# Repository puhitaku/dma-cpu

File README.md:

# dma-cpu

CPU made of DMA on Raspberry Pi Pico.

The DMA controller in the RP2 microcontroller family (RP2040, RP2350, and
compatible chips) is Turing-complete. This project builds a full toolchain
for it: an emulator, an assembler/linker, a program loader, a C compiler
riding stock clang, and an xv6-derived kernel that runs entirely on DMA
channels. See `prompts/overview.md` for the design analysis, the phased
development plan, and references.

## Layout

The tree is split by where code runs: `host/` is the Go toolchain that runs
on your dev machine, `target/` is the C that runs on the Pico. Everything
else is docs, examples, and vendored dependencies.

### `host/` — the Go toolchain

- `host/emu/` — `dmaemu` core: a deterministic, DMA-machine-level emulator
  of the RP2 DMA subsystem (channels, triggers, chaining, DREQ credits,
  pacing timers, sniffer, atomic register aliases). Both SKUs are
  supported via `emu.Variant` (`emu.RP2040`, `emu.RP2350`) — the CTRL bit
  layout, register offsets, sizes, and DREQ numbers differ between them,
  so programs are assembled per SKU. The golden tests in
  `host/emu/machine_test.go` build the machine's ALU and control-flow
  idioms block by block, run the whole suite on both SKUs, and prove out
  the interrupt-dispatch design from `prompts/overview.md` §3.2.
- `host/dmaasm/` — the assembler: SKU-portable `.dasm` sources (labels,
  literal pools, instruction-field addressing, the ABI v0 register file
  and macro instruction set — see `references/design_docs/abi.md`) assembled into
  SKU-specific DMX executables with a symbol table. Validated on silicon:
  the HIL firmware runs assembler-produced binaries.
- `host/dmacc/` + `host/llir/` — the C toolchain: `llir` parses clang's
  LLVM IR, `dmacc` lowers it to SKU-portable `.dasm`. Differential tests
  in `host/dmacc/testdata/` pin it against host clang.
- `host/trace/` + `host/pgo/` — the measurement side: `trace` attributes
  the emulator's per-word read counts back to code (compiled function,
  block, comparison site, runtime/millicode helper) through the `.dasm`
  label stream and prints a ranked report; `pgo` holds the generated
  profile-guided settings those measurements produce (`make pgo`).
  `host/dmacc/testdata/ratchet.txt` pins the resulting sizes and cycle
  counts, and `make test` fails on any drift (`make ratchet`).
- `host/img/` — the DMX executable format (`references/design_docs/dmx.md`): builder,
  encoder/decoder, and the reference loader with Tier-2 relocation (same
  image runs at any placement). `host/fsimg/` builds xv6 filesystem images
  and the golden vfat volumes.
- `host/boards/` — deployable-target descriptors (SKU, memory partition,
  flash sections, installed apps); `host/prog/hil/` holds the HIL test
  programs as embedded `.dasm` assets.
- `host/cmd/` — the CLIs: `dmaemu` (runs a raw block image or DMX
  executable under a JSON config, reporting JSON), `dmaasm`, `dmacc`,
  `dmxgen` (builds a board's images and bakes them, with their emulator
  expectations, into the firmware header), and `sldgen` (converts images
  into slides for the viewer).

### `target/` — bare-metal C for the Pico

- `target/loader/` — the DMX loader for the RP2 side; parses DMX,
  relocates, and starts the machine. No SDK dependency; build with
  `-DDMX_TARGET_RP2350` for RP2350 (RP2040 is the default). Validated on
  both SKUs' silicon.
- `target/firmware/` — the ARM-side bootloader: it sets the clocks,
  stages the flash-resident images, loads the SRAM segments through the
  loader, starts the DMA machine and parks. Built with `HIL_DEV=1` it
  also carries the hardware-in-the-loop battery, where `dmxgen` bakes
  emulator-computed expectations into the firmware and the boot run
  reports expected-vs-observed over UART. The emulator is
  silicon-calibrated against a Pico 2; see
  `prompts/004-hw-calibration.md` for the results (all golden tests pass
  on hardware at ~10 M blocks/s).
- `target/libc/` — the DMA machine's C library: DMA-specific config and
  glue (committed) plus the vendored picolibc submodule
  (`target/libc/picolibc`) it is compiled from. `make libc` turns the
  curated picolibc sources into the IR goldens in `target/libc/ll/`,
  which `dmacc` links into programs — see `target/libc/README.md`.
  `target/game/` is the DMA-driven game console; `target/xv6/` is the
  xv6-derived kernel port (`target/xv6/PORT.md`).

### Everything else

- `docs/` — human-facing guides: how to build the firmware
  (`building-firmware.md`) and how to wire the hardware
  (`building-hardware.md`).
- `prompts/` — the phased design log: the analysis in `overview.md` and a
  per-phase results document for each step.
- `references/` — material to consult, none of it compiled here:
  `datasheets/` (the RP2040/RP2350 and peripheral datasheets),
  `design_docs/` (the project's own specs — `abi.md` and `dmx.md`), and
  source trees read rather than built — some of them the origin of a port
  that now lives under `target/`, each attributed in `LICENSE`. Contrast
  `target/libc/picolibc`, which *is* compiled and linked. The reference
  article stays untracked (see Coding rules in `prompts/overview.md`).
- `examples/` — standalone programs built through the toolchain.
- `hw/` — KiCad project with JLCPCB-ready production data.

## Build and test

```console
$ make build   # builds bin/dmaemu, bin/dmaasm, bin/dmacc
$ make test    # go vet + golden tests
```

Requires Go ≥ 1.26. No dependencies outside the standard library.

## Special Thanks

This project is heavily inspired by [the original idea](https://people.ece.cornell.edu/land/courses/ece4760/RP2040/C_SDK_DMA_machine/DMA_machine_rp2040.html)
published by the authors in Cornell University.

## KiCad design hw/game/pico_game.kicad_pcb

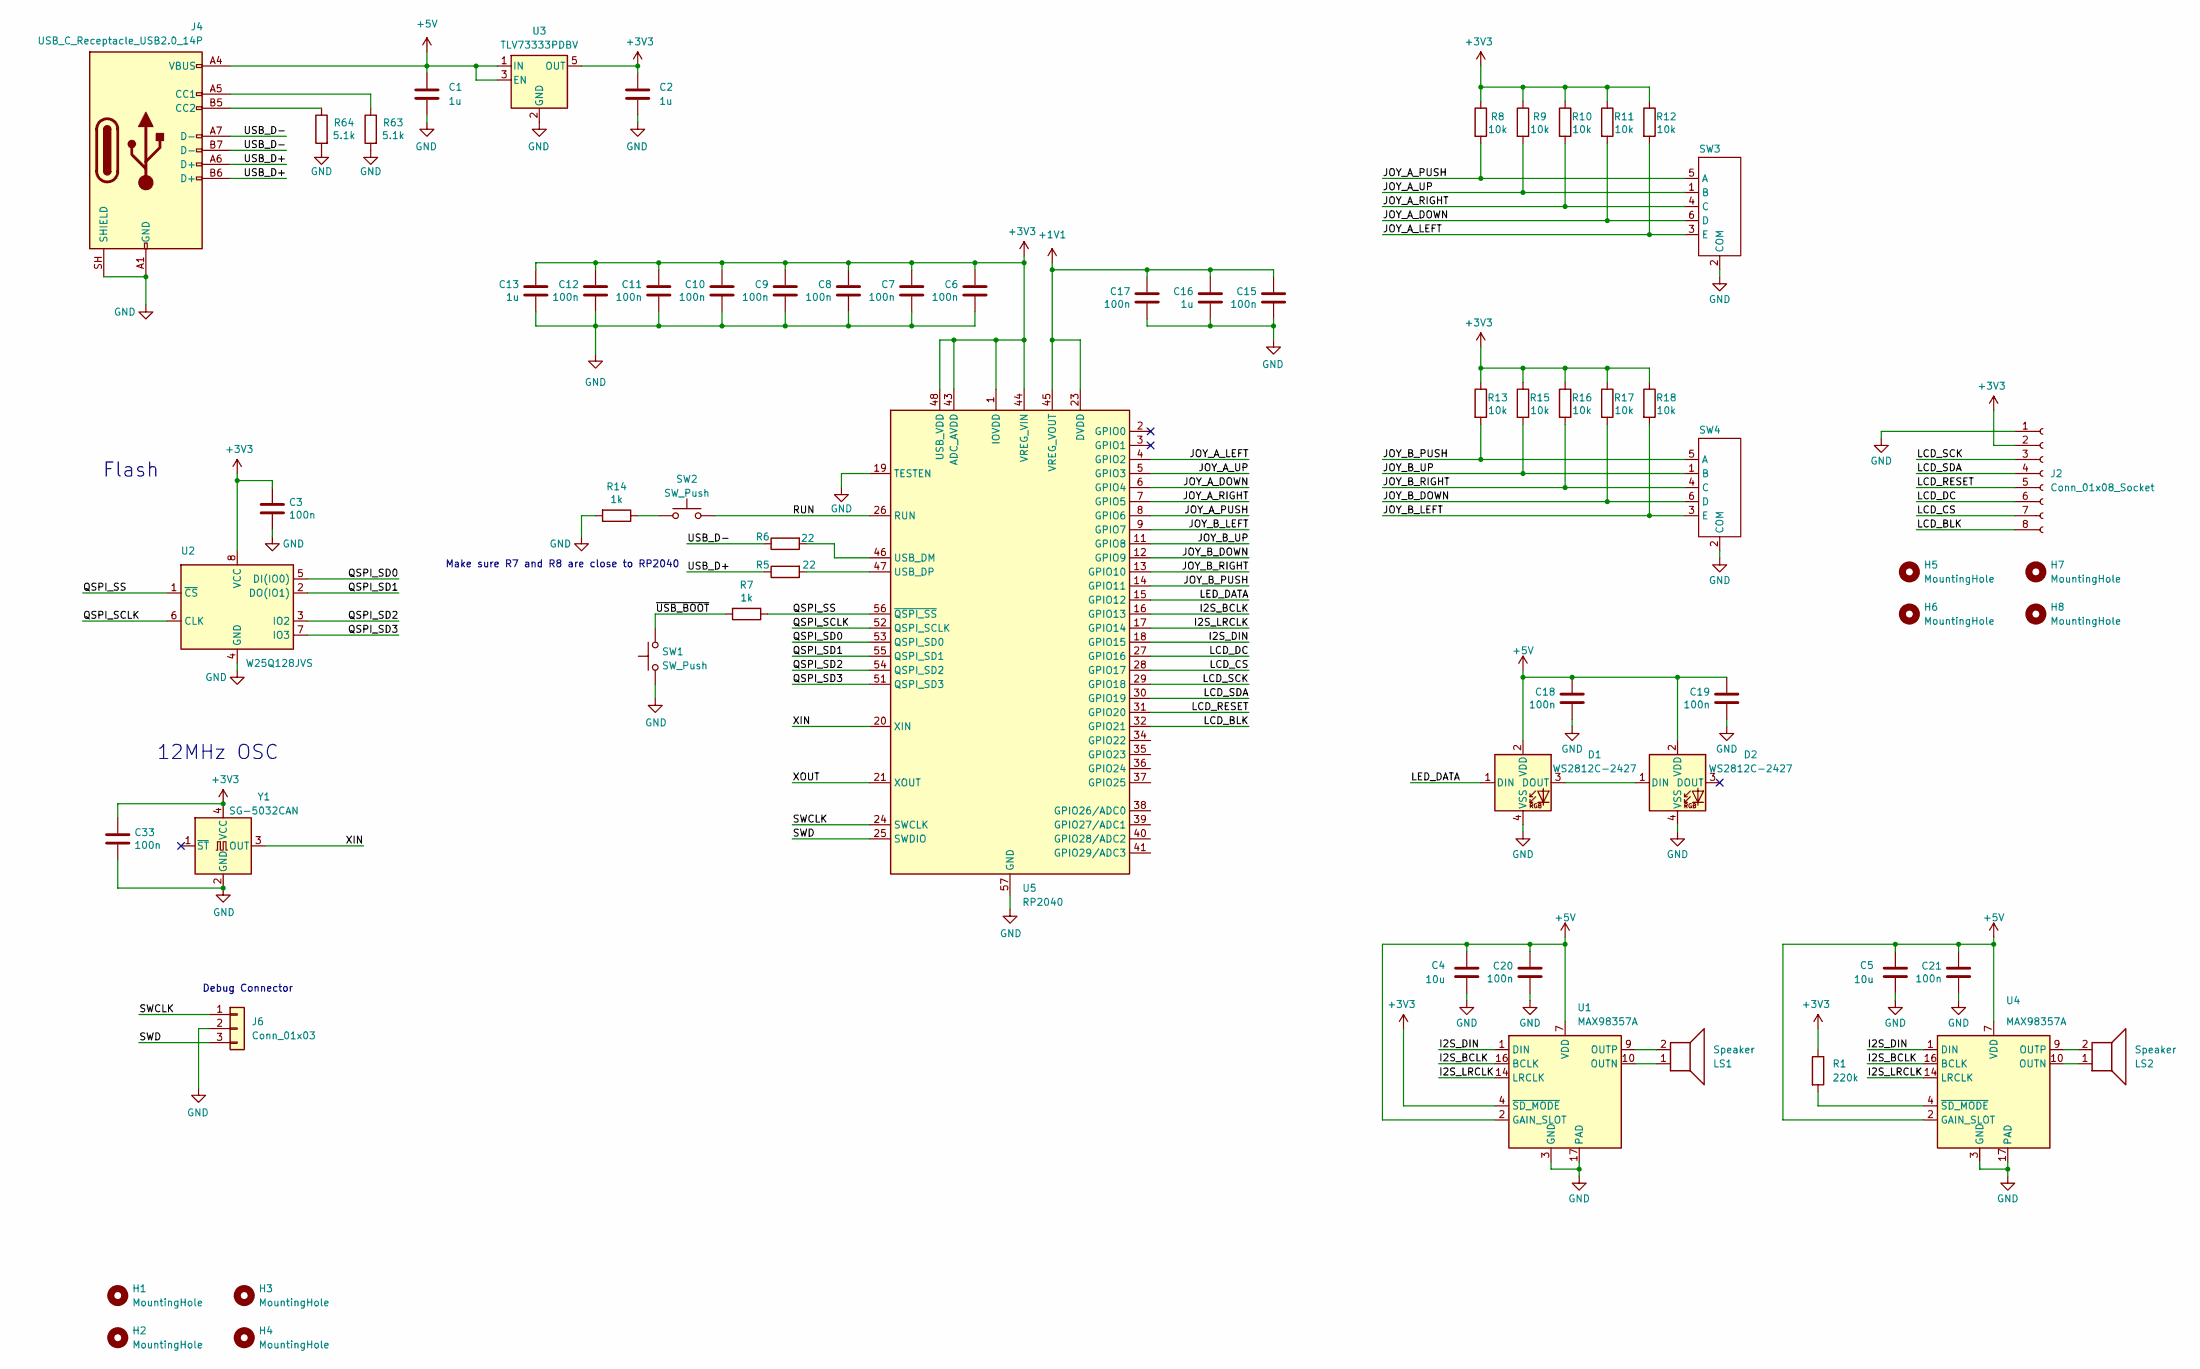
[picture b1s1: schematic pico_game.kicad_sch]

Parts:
C1, C2, C13, C16: 1u; C_0402_1005Metric; LCSC Part # C52923
C3, C6, C7, C8, C9, C10, C11, C12, C15, C17, C18, C19, C20, C21, C33: 100n; C_0402_1005Metric; LCSC Part # C307331
C4, C5: 10u; C_0603_1608Metric; LCSC Part # C96446
D1, D2: WS2812C-2427; LED_WS2812C-2427_PLCC4_2.4x2.7mm
H1, H2, H3, H4: MountingHole; MountingHole_3.2mm_M3
H5, H6, H7, H8: MountingHole; MountingHole_2.2mm_M2
J2: Conn_01x08_Socket; PinHeader_1x08_P2.54mm_Vertical
J4: USB_C_Receptacle_USB2.0_14P; USB_C_Receptacle_G-Switch_GT-USB-7010ASV; LCSC Part # C2988369
J6: Conn_01x03; PinSocket_1x03_P2.54mm_Vertical
LS1, LS2: Speaker; KLJ-01304T-08R07W; LCSC Part # C18186315
R1: 220k; R_0603_1608Metric; LCSC Part # C22961
R5, R6: 22; R_0402_1005Metric; LCSC Part # C25092
R7, R14: 1k; R_0402_1005Metric; LCSC Part # C11702
R8, R9, R10, R11, R12, R13, R15, R16, R17, R18: 10k; R_0402_1005Metric; LCSC Part # C25744
R63, R64: 5.1k; R_0402_1005Metric; LCSC Part # C25905
SW1, SW2: SW_Push; SW_SPST_TS-1088-xR020; LCSC Part # C720477
SW3, SW4: GT-TCA06F-H050-L1; LCSC Part # C3019725
U1, U4: MAX98357A; TQFN-16-1EP_3x3mm_P0.5mm_EP1.23x1.23mm; LCSC Part # C910544
U2: W25Q128JVS; SOIC-8_5.3x5.3mm_P1.27mm; LCSC Part # C97521
U3: TLV73333PDBV; SOT-23-5; LCSC Part # C134139
U5: RP2040; QFN-56-1EP_7x7mm_P0.4mm_EP3.2x3.2mm; LCSC Part # C2040
Y1: SG-5032CAN; Oscillator_SMD_SeikoEpson_SG210-4Pin_2.5x2.0mm; LCSC Part # C255991

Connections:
+1V1: C15.1, C16.1, C17.1, U5.23 (DVDD), U5.45 (VREG_VOUT), U5.50 (DVDD)
+3V3: C2.1, C3.1, C6.1, C7.1, C8.1, C9.1, C10.1, C11.1, C12.1, C13.1, C33.1, J2.2, R1.1, R8.1, R9.1, R10.1, R11.1, R12.1, R13.1, R15.1, R16.1, R17.1, R18.1, U1.4 (~SD_MODE), U2.8 (VCC), U3.5 (OUT), U5.1 (IOVDD), U5.10 (IOVDD), U5.22 (IOVDD), U5.33 (IOVDD), U5.42 (IOVDD), U5.43 (ADC_AVDD), U5.44 (VREG_VIN), U5.48 (USB_VDD), U5.49 (IOVDD), Y1.4 (VCC)
+5V: C1.1, C4.1, C5.1, C18.1, C19.1, C20.1, C21.1, D1.2 (VDD), D2.2 (VDD), J4.A4 (VBUS), J4.A9 (VBUS), J4.B4 (VBUS), J4.B9 (VBUS), U1.2 (GAIN_SLOT), U1.7 (VDD), U1.8 (VDD), U3.1 (IN), U3.3 (EN), U4.2 (GAIN_SLOT), U4.7 (VDD), U4.8 (VDD)
/I2S_BCLK: U1.16 (BCLK), U4.16 (BCLK), U5.16 (GPIO13)
/I2S_DIN: U1.1 (DIN), U4.1 (DIN), U5.18 (GPIO15)
/I2S_LRCLK: U1.14 (LRCLK), U4.14 (LRCLK), U5.17 (GPIO14)
/JOY_A_DOWN: R11.2, SW3.6 (D), U5.6 (GPIO4)
/JOY_A_LEFT: R12.2, SW3.3 (E), U5.4 (GPIO2)
/JOY_A_PUSH: R8.2, SW3.5 (A), U5.8 (GPIO6)
/JOY_A_RIGHT: R10.2, SW3.4 (C), U5.7 (GPIO5)
/JOY_A_UP: R9.2, SW3.1 (B), U5.5 (GPIO3)
/JOY_B_DOWN: R17.2, SW4.6 (D), U5.12 (GPIO9)
/JOY_B_LEFT: R18.2, SW4.3 (E), U5.9 (GPIO7)
/JOY_B_PUSH: R13.2, SW4.5 (A), U5.14 (GPIO11)
/JOY_B_RIGHT: R16.2, SW4.4 (C), U5.13 (GPIO10)
/JOY_B_UP: R15.2, SW4.1 (B), U5.11 (GPIO8)
/LCD_BLK: J2.8, U5.32 (GPIO21)
/LCD_CS: J2.7, U5.28 (GPIO17)
/LCD_DC: J2.6, U5.27 (GPIO16)
/LCD_RESET: J2.5, U5.31 (GPIO20)
/LCD_SCK: J2.3, U5.29 (GPIO18)
/LCD_SDA: J2.4, U5.30 (GPIO19)
/LED_DATA: D1.1 (DIN), U5.15 (GPIO12)
/QSPI_SCLK: U2.6 (CLK), U5.52 (QSPI_SCLK)
/QSPI_SD0: U2.5 (DI(IO0)), U5.53 (QSPI_SD0)
/QSPI_SD1: U2.2 (DO(IO1)), U5.55 (QSPI_SD1)
/QSPI_SD2: U2.3 (IO2), U5.54 (QSPI_SD2)
/QSPI_SD3: U2.7 (IO3), U5.51 (QSPI_SD3)
/QSPI_SS: R7.1, U2.1 (~CS), U5.56 (~QSPI_SS)
/RUN: SW2.2, U5.26 (RUN)
/SWCLK: J6.1, U5.24 (SWCLK)
/SWD: J6.3, U5.25 (SWDIO)
/USB_D+: J4.A6 (D+), J4.B6 (D+), R5.1
/USB_D-: J4.A7 (D-), J4.B7 (D-), R6.1
/XIN: U5.20 (XIN), Y1.3 (OUT)
/XOUT: U5.21 (XOUT)
/~USB_BOOT: R7.2, SW1.2
GND: C1.2, C2.2, C3.2, C4.2, C5.2, C6.2, C7.2, C8.2, C9.2, C10.2, C11.2, C12.2, C13.2, C15.2, C16.2, C17.2, C18.2, C19.2, C20.2, C21.2, C33.2, D1.4 (VSS), D2.4 (VSS), J2.1, J4.A1 (GND), J4.A12 (GND), J4.B1 (GND), J4.B12 (GND), J4.SH (SHIELD), J6.2, R14.2, R63.2, R64.2, SW1.1, SW3.2 (COM), SW4.2 (COM), U1.3 (GND), U1.11 (GND), U1.15 (GND), U1.17 (PAD), U2.4 (GND), U3.2 (GND), U4.3 (GND), U4.11 (GND), U4.15 (GND), U4.17 (PAD), U5.19 (TESTEN), U5.57 (GND), Y1.2 (GND)
unnamed: D1.3 (DOUT), D2.1 (DIN)
unnamed: J4.A5 (CC1), R63.1
unnamed: J4.B5 (CC2), R64.1
unnamed: R14.1, SW2.1
unnamed: LS1.1, U1.10 (OUTN)
unnamed: LS1.2, U1.9 (OUTP)
unnamed: LS2.1, U4.10 (OUTN)
unnamed: LS2.2, U4.9 (OUTP)
unnamed: R1.2, U4.4 (~SD_MODE)
unnamed: R6.2, U5.46 (USB_DM)
unnamed: R5.2, U5.47 (USB_DP)

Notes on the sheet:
Flash
12MHz OSC
Debug Connector
Make sure R7 and R8 are close to RP2040

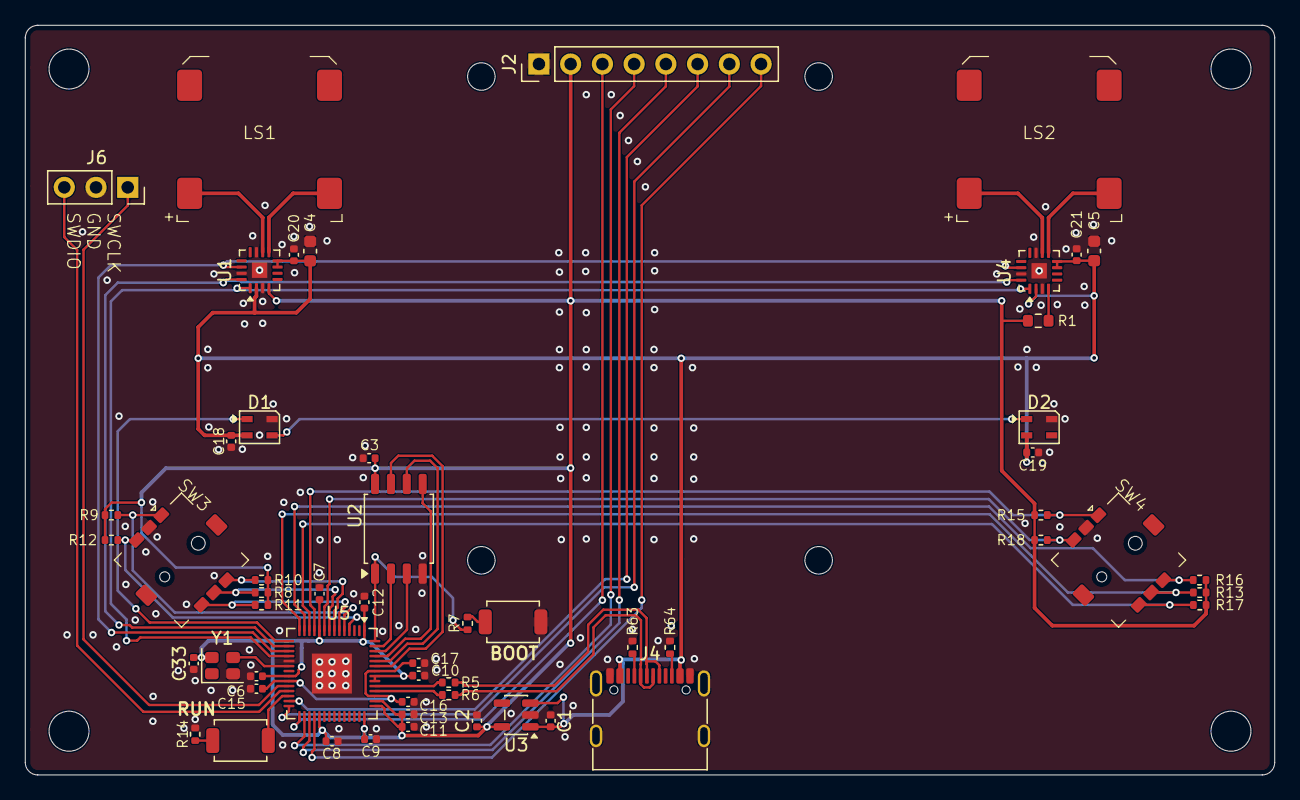
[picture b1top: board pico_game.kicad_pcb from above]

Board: 2 copper layers, 100.0 x 60.0 mm, 63 parts (0 on the bottom side), 48 nets.

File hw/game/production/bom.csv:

Designator,Footprint,Quantity,Value,LCSC Part #
"C1, C13, C16, C2",0402,4,1u,C52923
"C10, C11, C12, C15, C17, C18, C19, C20, C21, C3, C33, C6, C7, C8, C9",0402,15,100n,C307331
"C4, C5",0603,2,10u,C96446
"D1, D2",LED_WS2812C-2427_PLCC4_2.4x2.7mm,2,WS2812C-2427,
J2,PinHeader_1x08_P2.54mm_Vertical,1,Conn_01x08_Socket,
J4,USB_C_Receptacle_G-Switch_GT-USB-7010ASV,1,USB_C_Receptacle_USB2.0_14P,C2988369
J6,PinSocket_1x03_P2.54mm_Vertical,1,Conn_01x03,
"LS1, LS2",KLJ-01304T-08R07W,2,Speaker,C18186315
R1,0603,1,220k,C22961
"R10, R11, R12, R13, R15, R16, R17, R18, R8, R9",0402,10,10k,C25744
"R14, R7",0402,2,1k,C11702
"R5, R6",0402,2,22,C25092
"R63, R64",0402,2,5.1k,C25905
"SW1, SW2",SW_SPST_TS-1088-xR020,2,SW_Push,C720477
"SW3, SW4",GT-TCA06F-H050-L1,2,~,C3019725
"U1, U4",TQFN-16-1EP_3x3mm_P0.5mm_EP1.23x1.23mm,2,MAX98357A,C910544
U2,SOIC-8_5.3x5.3mm_P1.27mm,1,W25Q128JVS,C97521
U3,SOT-23-5,1,TLV73333PDBV,C134139
U5,QFN-56-1EP_7x7mm_P0.4mm_EP3.2x3.2mm,1,RP2040,C2040
Y1,Oscillator_SMD_SeikoEpson_SG210-4Pin_2.5x2.0mm,1,SG-5032CAN,C255991

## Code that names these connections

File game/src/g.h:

/* g.h: the gamepico bare-metal runtime's one header. No xv6, no libc
 * — the DMA machine drives every peripheral register itself, and the
 * ARM cores sleep. Register addresses are RP2040's (this board is
 * SKU-locked; the emulator models the same map). */
#ifndef GAME_G_H
#define GAME_G_H

typedef unsigned int uint;
typedef unsigned short ushort;
typedef unsigned char uchar;

#define W32(a) (*(volatile uint *)(a))

/* --- RP2040 fixed addresses --- */
#define IOBANK0 0x40014000u
#define PADSBANK0 0x4001C000u
#define TIMERAWL 0x40054028u /* microsecond counter, low word */
#define SPI0 0x4003C000u     /* PL022: CR0 +0, CR1 +4, DR +8, SR +C, CPSR +10 */
#define DMACH(n) (0x50000000u + (uint)(n) * 0x40u)

/* --- board wiring (see prompts/040) ---
 * Joysticks occupy GP2..GP11 but NOT in role order — the as-built
 * harness (input.c holds the tables):
 *   A: up=GP3 down=GP4 left=GP2 right=GP5 press=GP6
 *   B: up=GP8 down=GP9 left=GP7 right=GP10 press=GP11 */
#define PIN_WS 12     /* two chained WS2811 */
#define PIN_I2S_BCLK 13
#define PIN_I2S_LRCLK 14
#define PIN_I2S_DIN 15
#define PIN_LCD_DC 16
#define PIN_LCD_CS 17
#define PIN_LCD_SCK 18
#define PIN_LCD_SDA 19
#define PIN_LCD_RES 20
#define PIN_LCD_BLK 21

#define LCD_W 240
#define LCD_H 240

/* grt.c: runtime */
void uputs(const char *s);
void uputn(uint v);
void uputhex(uint v);
void numstr(char *buf, int width, uint v); /* zero-padded decimal */
void numsp(char *buf, int width, uint v);  /* space-padded decimal */
uint now_us(void);
void delay_us(uint us);
void gpio_fn(int pin, uint funcsel);
void gpio_out(int pin, int hi);
void gpio_in_init(int pin); /* enable the pull-up, once */
uint gpio_in(int pin);      /* raw masked level: nonzero = high */
void gdma_copy(uint dst, uint src, uint bytes);
void gdma_fill(uint dst, uint word, uint bytes);
void gdma_spi16(uint src, uint halfwords); /* paced pixel stream */
void gdma_rows(uint dst, uint src, uint words, int rows, uint dstride,
               uint sstride); /* 2-write row loop (AL3 trigger) */
void gdma_spi_rows(uint src, uint halfwords, int rows,
                   uint sstride); /* 1-write row loop into the SPI */

/* lcd.c */
void lcd_init(void);
void lcd_flush(int x0, int y0, int x1, int y1); /* inclusive rect */

/* gfx.c */
extern ushort fb[LCD_W * LCD_H];
void gfx_clear(ushort c);
void gfx_fill(int x0, int y0, int w, int h, ushort c);
void gfx_rect(int x0, int y0, int w, int h, int t, ushort c); /* outline */
void gfx_text(int x, int y, const char *s, ushort fg, ushort bg);
void gfx_text2(int x, int y, const char *s, ushort fg, ushort bg); /* 2x */
void gfx_blit(int x, int y, const ushort *src, int w, int h); /* opaque */
void gfx_sprite(const uint *rows, int w, int h, ushort fg, ushort bg,
                ushort *dst); /* 1bpp rows (MSB left) -> RGB565 */
void gfx_glyph_cell(int ch, ushort fg, ushort bg,
                    ushort *dst); /* one 8x8 font glyph -> 64 pixels */
void gfx_damage(int x0, int y0, int x1, int y1);
void gfx_present(void); /* flush the damage rect, reset it */

/* input.c: both joysticks merged, active-high bit set = engaged */
#define BTN_UP 0x01
#define BTN_DOWN 0x02
#define BTN_LEFT 0x04
#define BTN_RIGHT 0x08
#define BTN_A 0x10
extern uint in_down; /* held buttons */
extern uint in_edge; /* newly pressed since the previous poll */
void in_poll(void);
uint rng(void);           /* xorshift32, mixed with input timing */
uint rng_below(uint n);   /* uniform-ish 0..n-1 */
void frame_sync(uint us); /* pace the caller's loop to one tick per us */

/* fx.c: sound (PIO0 SM0 I2S + ring-streaming DMA) and light (PIO0
 * SM1 WS2811). snd_tick runs from frame_sync, so a tone's frame
 * budget counts in every loop that paces itself.
 * The audio ring is 16 KiB at a fixed 16 KiB-aligned address (the
 * ring wrap is an address mask): 4096 L|R frames, which is also one
 * sequencer step. Reserved region 0x2002C000..0x2003C000 holds the
 * drum PCM then the ring; dmxgen asserts the image stays clear. */
#define AURING 0x20038000u
#define AURING_BYTES 16384u
void fx_init(void);
void snd_play(uint hz, uint vol, uint frames); /* vol 0..255 */
void snd_rate(uint div_fp8); /* SM0 CLKDIV, keep 15900..26300 in-band */
void snd_off(void); /* silence immediately */
extern uint sfx_tab[4]; /* {addr,samples} x {dino_fail, lanwalk_success} */
void pcm_play(uint addr, uint samples); /* mono 16-bit clip from flash */
void pcm_stop(void);
void pcm_tick(void);
void snd_tick(void);
void led(uint rgb0, uint rgb1); /* 0xRRGGBB each; per-channel capped */
void led_rainbow(uint frames);   /* fast hue loop, then back to base */
void led_blink(uint rgb, uint cycles); /* tri-ramp blink, 4 f/side */
void led_tick(void); /* frame_sync drives the animations */

/* Global LED brightness tiers: write call sites with full-saturation
 * colors and wrap them — the scale plus led()'s hard cap keeps both
 * WS2811s even and comfortable everywhere. */
#define LED_BRIGHT(c) (((c) >> 2) & 0x3F3F3F)
#define LED_DIM(c) (((c) >> 4) & 0x0F0F0F)
void seq_run(void); /* the percussion sequencer demo */

/* the games (each returns when the player exits to the menu) */
int menu_run(void); /* 0 Dino 1 LANWalk 2 Yacht 3 Seq 4 CPUmon */
void dino_run(void);
void lanwalk_run(void);
void yacht_run(void);
void cpumon_run(void); /* the "CPU is asleep" monitor */

#define RGB(r, g, b) \
  ((ushort)((((r) & 0xF8) << 8) | (((g) & 0xFC) << 3) | (((b) & 0xF8) >> 3)))

#endif

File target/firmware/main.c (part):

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 *    initializes after the switch (clk_usb/clk_adc die: unused).
 *  - HSTX TMDS encoder in RGB332, 4 pixels per FIFO word (the
 *    pico-examples dvi_out_hstx_encoder configuration).
 *  - Board pin map: HSTX bit N = GPIO 12+N; clock pair GPIO14/15,
 *    lane0 GPIO18/19, lane1 GPIO16/17, lane2 GPIO12/13.
 * PSRAM (QMI CS1, GPIO8) is brought up by the SDK runtime init
 * (hardware_psram), including XIP_CTRL.WRITABLE_M1 for writes. */
static void feather_video_init(void)
{
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        2u << HSTX_CTRL_CSR_SHIFT_LSB |
        HSTX_CTRL_CSR_EN_BITS;

    /* Clock pair on HSTX bits 2/3 (GPIO14/15). */
    hstx_ctrl_hw->bit[2] = HSTX_CTRL_BIT0_CLK_BITS;
    hstx_ctrl_hw->bit[3] = HSTX_CTRL_BIT0_CLK_BITS | HSTX_CTRL_BIT0_INV_BITS;
    /* TMDS lane -> HSTX bit of its positive pin: D0=GPIO18, D1=GPIO16,
     * D2=GPIO12. Even shifter bits leave in the first half-cycle. */
    static const int lane_bit[3] = {6, 4, 0};
    for (int lane = 0; lane < 3; lane++) {
        int bit = lane_bit[lane];
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    gpio_pull_up(SD_MISO); /* DAT0 wants a pull during high-Z gaps */
    gpio_pull_up(SD_MOSI);
    /* Quietest pads that still clock the card: the SD lines run on
     * GPIO20/22/23, right beside the HSTX TMDS lanes (GPIO12-19), and
     * the borrow's gapless 25 MHz bursts at hot pads cost the display
     * its sync (bisected on silicon: machine-fed TX clean, wire-speed
     * borrow noisy at identical firmware). */
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     * is not launched and stays asleep in the bootrom's wfe loop. */
#endif

    /* GPIO2: input from the firmware's view; the DMA machine drives it
     * via IO_BANK0 overrides. gpio_init also clears RP2350 pad isolation. */
    gpio_init(2);
    gpio_set_dir(2, false);
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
